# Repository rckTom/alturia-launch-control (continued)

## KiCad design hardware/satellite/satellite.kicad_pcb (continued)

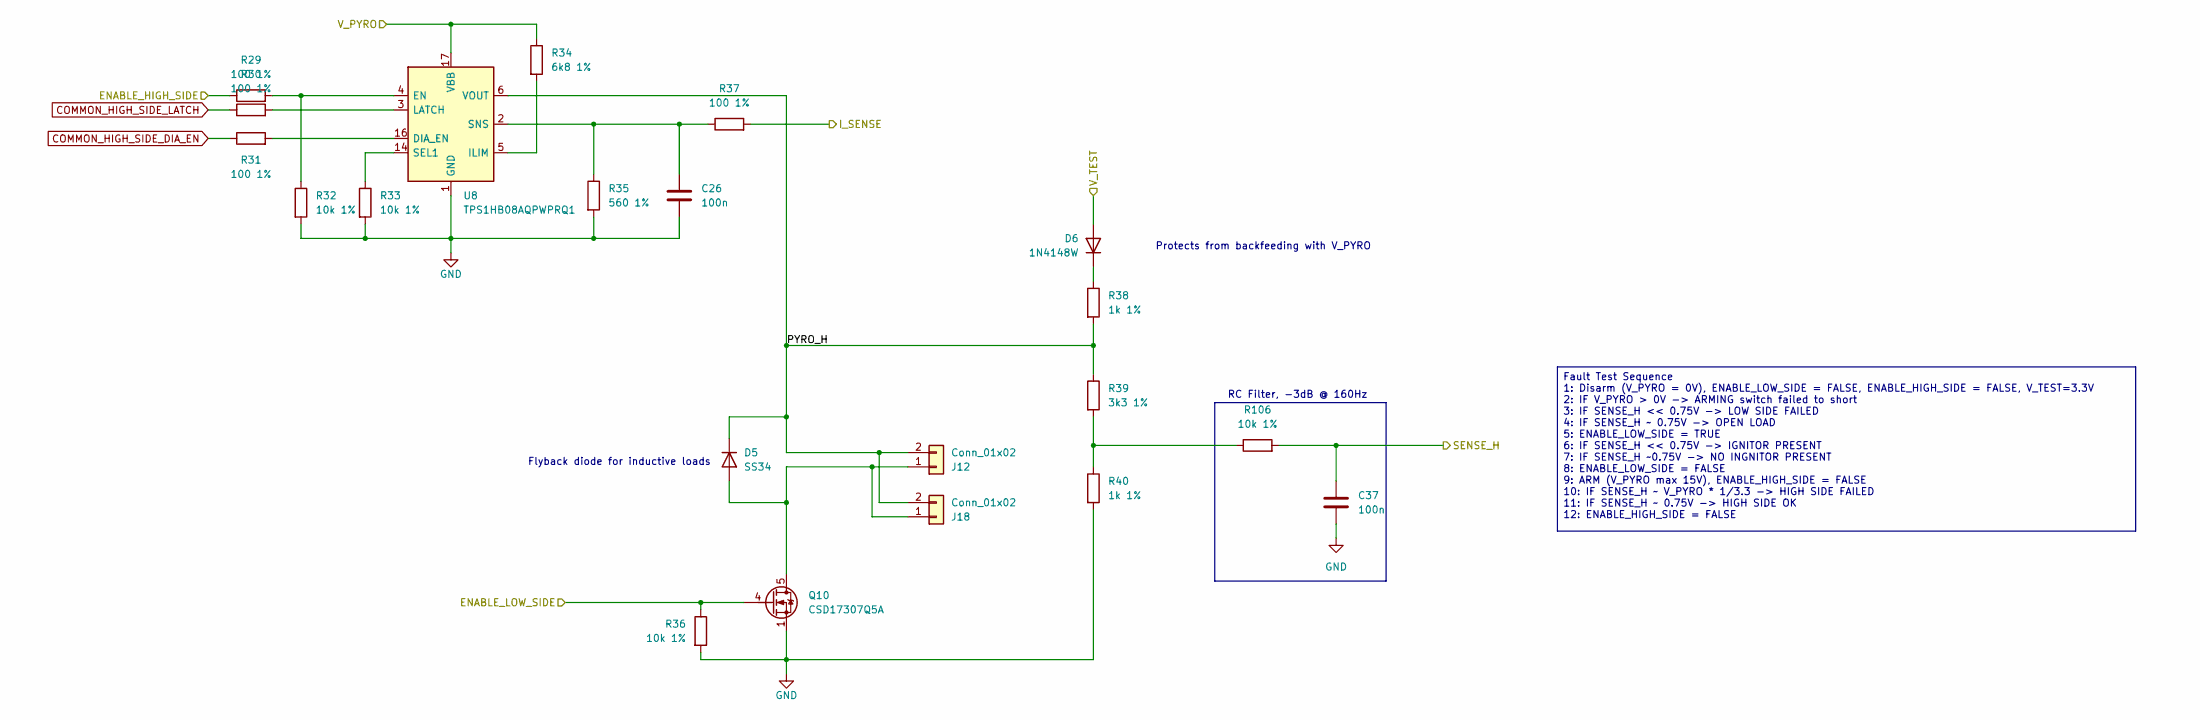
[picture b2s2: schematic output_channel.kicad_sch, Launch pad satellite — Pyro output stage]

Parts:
C26, C37: 100n; C_0603_1608Metric; LCSC C14663
D5: SS34; D_SMA; LCSC C8678
D6: 1N4148W; D_SOD-123; LCSC C81598
J12: Conn_01x02; TerminalBlock_CUI_TB007-508-02_1x02_P5.08mm_Horizontal
J18: Conn_01x02; BananJack
Q10: CSD17307Q5A; TDSON-8-1; LCSC C139362
R29, R30, R31, R37: 100 1%; R_0603_1608Metric; LCSC C22775
R32, R33, R36, R106: 10k 1%; R_0603_1608Metric; LCSC C25804
R34: 6k8 1%; R_0603_1608Metric; LCSC C23212
R35: 560 1%; R_0603_1608Metric; LCSC C23204
R38, R40: 1k 1%; R_0603_1608Metric; LCSC C21190
R39: 3k3 1%; R_0603_1608Metric; LCSC C22978
U8: TPS1HB08AQPWPRQ1; HTSSOP-16-1EP_4.4x5mm_P0.65mm_EP3.4x5mm_Mask2.78x3.37mm_The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; MPN TPS1HB08AQPWPRQ1; LCSC Part C3019223

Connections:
/PyroStage3/PYRO_H: D5.1 (K), J12.2, J18.2, R38.2, R39.1, U8.6 (VOUT), U8.7 (VOUT), U8.8 (VOUT), U8.9 (VOUT), U8.10 (VOUT), U8.11 (VOUT)
COMMON_HIGH_SIDE_DIA_EN: R31.1; also elsewhere on the board
COMMON_HIGH_SIDE_LATCH: R30.1; also elsewhere on the board
ENABLE_P3_HIGH: R29.1; also elsewhere on the board
ENABLE_P3_LOW: Q10.4 (G), R36.1; also elsewhere on the board
GND: C26.2, C37.2, Q10.1 (S), Q10.2 (S), Q10.3 (S), R32.2, R33.2, R35.2, R36.2, R40.2, U8.1 (GND); also elsewhere on the board
unnamed: D5.2 (A), J12.1, J18.1, Q10.5 (D)
unnamed: D6.1 (K), R38.1
unnamed: R39.2, R40.1, R106.1
unnamed: R31.2, U8.16 (DIA_EN)
unnamed: R29.2, R32.1, U8.4 (EN)
unnamed: R34.2, U8.5 (ILIM)
unnamed: R30.2, U8.3 (LATCH)
unnamed: R33.1, U8.14 (SEL1)
unnamed: C26.1, R35.1, R37.1, U8.2 (SNS)
SENSE_H_P3: C37.1, R106.2; also elsewhere on the board
SENSE_I_P3: R37.2; also elsewhere on the board
V_PYRO_ARMED: R34.1, U8.17 (VBB); also elsewhere on the board
V_TEST: D6.2 (A); also elsewhere on the board

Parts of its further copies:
C27, C28, C29, C35, C36, C38, C39, C40, C41, C42: 100n; C_0603_1608Metric; LCSC C14663
D7, D9, D11, D13, D15: SS34; D_SMA; LCSC C8678
D8, D10, D12, D14, D16: 1N4148W; D_SOD-123; LCSC C81598
J13, J14, J15, J16, J17: Conn_01x02; TerminalBlock_CUI_TB007-508-02_1x02_P5.08mm_Horizontal
J19, J20, J21, J22, J23: Conn_01x02; BananJack
Q11, Q12, Q13, Q14, Q15: CSD17307Q5A; TDSON-8-1; LCSC C139362
R41, R42, R43, R49, R53, R54, R55, R61, R65, R66, R67, R73, R77, R78, R79, R85, R89, R90, R91, R97: 100 1%; R_0603_1608Metric; LCSC C22775
R44, R45, R48, R56, R57, R60, R68, R69, R72, R80, R81, R84, R92, R93, R96, R107, R108, R109, R110, R111: 10k 1%; R_0603_1608Metric; LCSC C25804
R46, R58, R70, R82, R94: 6k8 1%; R_0603_1608Metric; LCSC C23212
R47, R59, R71, R83, R95: 560 1%; R_0603_1608Metric; LCSC C23204
R50, R52, R62, R64, R74, R76, R86, R88, R98, R100: 1k 1%; R_0603_1608Metric; LCSC C21190
R51, R63, R75, R87, R99: 3k3 1%; R_0603_1608Metric; LCSC C22978
U9, U10, U11, U14, U15: TPS1HB08AQPWPRQ1; HTSSOP-16-1EP_4.4x5mm_P0.65mm_EP3.4x5mm_Mask2.78x3.37mm_The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; MPN TPS1HB08AQPWPRQ1; LCSC Part C3019223

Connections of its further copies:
/PyroStage1/PYRO_H: D15.1 (K), J17.2, J23.2, R98.2, R99.1, U15.6 (VOUT), U15.7 (VOUT), U15.8 (VOUT), U15.9 (VOUT), U15.10 (VOUT), U15.11 (VOUT)
/PyroStage2/PYRO_H: D13.1 (K), J16.2, J22.2, R86.2, R87.1, U14.6 (VOUT), U14.7 (VOUT), U14.8 (VOUT), U14.9 (VOUT), U14.10 (VOUT), U14.11 (VOUT)
/PyroStage4/PYRO_H: D7.1 (K), J13.2, J19.2, R50.2, R51.1, U9.6 (VOUT), U9.7 (VOUT), U9.8 (VOUT), U9.9 (VOUT), U9.10 (VOUT), U9.11 (VOUT)
/PyroStage5/PYRO_H: D9.1 (K), J14.2, J20.2, R62.2, R63.1, U10.6 (VOUT), U10.7 (VOUT), U10.8 (VOUT), U10.9 (VOUT), U10.10 (VOUT), U10.11 (VOUT)
/PyroStage6/PYRO_H: D11.1 (K), J15.2, J21.2, R74.2, R75.1, U11.6 (VOUT), U11.7 (VOUT), U11.8 (VOUT), U11.9 (VOUT), U11.10 (VOUT), U11.11 (VOUT)
COMMON_HIGH_SIDE_DIA_EN: R43.1, R55.1, R67.1, R79.1, R91.1; also elsewhere on the board
COMMON_HIGH_SIDE_LATCH: R42.1, R54.1, R66.1, R78.1, R90.1; also elsewhere on the board
ENABLE_P1_HIGH: R89.1; also elsewhere on the board
ENABLE_P1_LOW: Q15.4 (G), R96.1; also elsewhere on the board
ENABLE_P2_HIGH: R77.1; also elsewhere on the board
ENABLE_P2_LOW: Q14.4 (G), R84.1; also elsewhere on the board
ENABLE_P4_HIGH: R41.1; also elsewhere on the board
ENABLE_P4_LOW: Q11.4 (G), R48.1; also elsewhere on the board
ENABLE_P5_HIGH: R53.1; also elsewhere on the board
ENABLE_P5_LOW: Q12.4 (G), R60.1; also elsewhere on the board
ENABLE_P6_HIGH: R65.1; also elsewhere on the board
ENABLE_P6_LOW: Q13.4 (G), R72.1; also elsewhere on the board
GND: C27.2, C28.2, C29.2, C35.2, C36.2, C38.2, C39.2, C40.2, C41.2, C42.2, Q11.1 (S), Q11.2 (S), Q11.3 (S), Q12.1 (S), Q12.2 (S), Q12.3 (S), Q13.1 (S), Q13.2 (S), Q13.3 (S), Q14.1 (S), Q14.2 (S), Q14.3 (S), Q15.1 (S), Q15.2 (S), Q15.3 (S), R44.2, R45.2, R47.2, R48.2, R52.2, R56.2, R57.2, R59.2, R60.2, R64.2, R68.2, R69.2, R71.2, R72.2, R76.2, R80.2, R81.2, R83.2, R84.2, R88.2, R92.2, R93.2, R95.2, R96.2, R100.2, U9.1 (GND), U10.1 (GND), U11.1 (GND), U14.1 (GND), U15.1 (GND); also elsewhere on the board
unnamed: D7.2 (A), J13.1, J19.1, Q11.5 (D)
unnamed: D8.1 (K), R50.1
unnamed: D9.2 (A), J14.1, J20.1, Q12.5 (D)
unnamed: D10.1 (K), R62.1
unnamed: D11.2 (A), J15.1, J21.1, Q13.5 (D)
unnamed: D12.1 (K), R74.1
unnamed: D13.2 (A), J16.1, J22.1, Q14.5 (D)
unnamed: D14.1 (K), R86.1
unnamed: D15.2 (A), J17.1, J23.1, Q15.5 (D)
unnamed: D16.1 (K), R98.1
unnamed: R99.2, R100.1, R111.1
unnamed: R51.2, R52.1, R107.1
unnamed: R63.2, R64.1, R108.1
unnamed: R75.2, R76.1, R109.1
unnamed: R87.2, R88.1, R110.1
unnamed: R43.2, U9.16 (DIA_EN)
unnamed: R41.2, R44.1, U9.4 (EN)
unnamed: R46.2, U9.5 (ILIM)
unnamed: R42.2, U9.3 (LATCH)
unnamed: R45.1, U9.14 (SEL1)
unnamed: C27.1, R47.1, R49.1, U9.2 (SNS)
unnamed: R55.2, U10.16 (DIA_EN)
unnamed: R53.2, R56.1, U10.4 (EN)
unnamed: R58.2, U10.5 (ILIM)
unnamed: R54.2, U10.3 (LATCH)
unnamed: R57.1, U10.14 (SEL1)
unnamed: C28.1, R59.1, R61.1, U10.2 (SNS)
unnamed: R67.2, U11.16 (DIA_EN)
unnamed: R65.2, R68.1, U11.4 (EN)
unnamed: R70.2, U11.5 (ILIM)
unnamed: R66.2, U11.3 (LATCH)
unnamed: R69.1, U11.14 (SEL1)
unnamed: C29.1, R71.1, R73.1, U11.2 (SNS)
unnamed: R79.2, U14.16 (DIA_EN)
unnamed: R77.2, R80.1, U14.4 (EN)
unnamed: R82.2, U14.5 (ILIM)
unnamed: R78.2, U14.3 (LATCH)
unnamed: R81.1, U14.14 (SEL1)
unnamed: C35.1, R83.1, R85.1, U14.2 (SNS)
unnamed: R91.2, U15.16 (DIA_EN)
unnamed: R89.2, R92.1, U15.4 (EN)
unnamed: R94.2, U15.5 (ILIM)
unnamed: R90.2, U15.3 (LATCH)
unnamed: R93.1, U15.14 (SEL1)
unnamed: C36.1, R95.1, R97.1, U15.2 (SNS)
SENSE_H_P1: C42.1, R111.2; also elsewhere on the board
SENSE_H_P2: C41.1, R110.2; also elsewhere on the board
SENSE_H_P4: C38.1, R107.2; also elsewhere on the board
SENSE_H_P5: C39.1, R108.2; also elsewhere on the board
SENSE_H_P6: C40.1, R109.2; also elsewhere on the board
SENSE_I_P1: R97.2; also elsewhere on the board
SENSE_I_P2: R85.2; also elsewhere on the board
SENSE_I_P4: R49.2; also elsewhere on the board
SENSE_I_P5: R61.2; also elsewhere on the board
SENSE_I_P6: R73.2; also elsewhere on the board
V_PYRO_ARMED: R46.1, R58.1, R70.1, R82.1, R94.1, U9.17 (VBB), U10.17 (VBB), U11.17 (VBB), U14.17 (VBB), U15.17 (VBB); also elsewhere on the board
V_TEST: D8.2 (A), D10.2 (A), D12.2 (A), D14.2 (A), D16.2 (A); also elsewhere on the board

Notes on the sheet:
Protects from backfeeding with V_PYRO
Flyback diode for inductive loads
RC Filter, -3dB @ 160Hz
Fault Test Sequence 1: Disarm (V_PYRO = 0V), ENABLE_LOW_SIDE = FALSE, ENABLE_HIGH_SIDE = FALSE, V_TEST=3.3V 2: IF V_PYRO > 0V -> ARMING switch failed to short 3: IF SENSE_H << 0.75V -> LOW SIDE FAILED 4: IF SENSE_H ~ 0.75V -> OPEN LOAD 5: ENABLE_LOW_SIDE = TRUE 6: IF SENSE_H << 0.75V -> IGNITOR PRE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

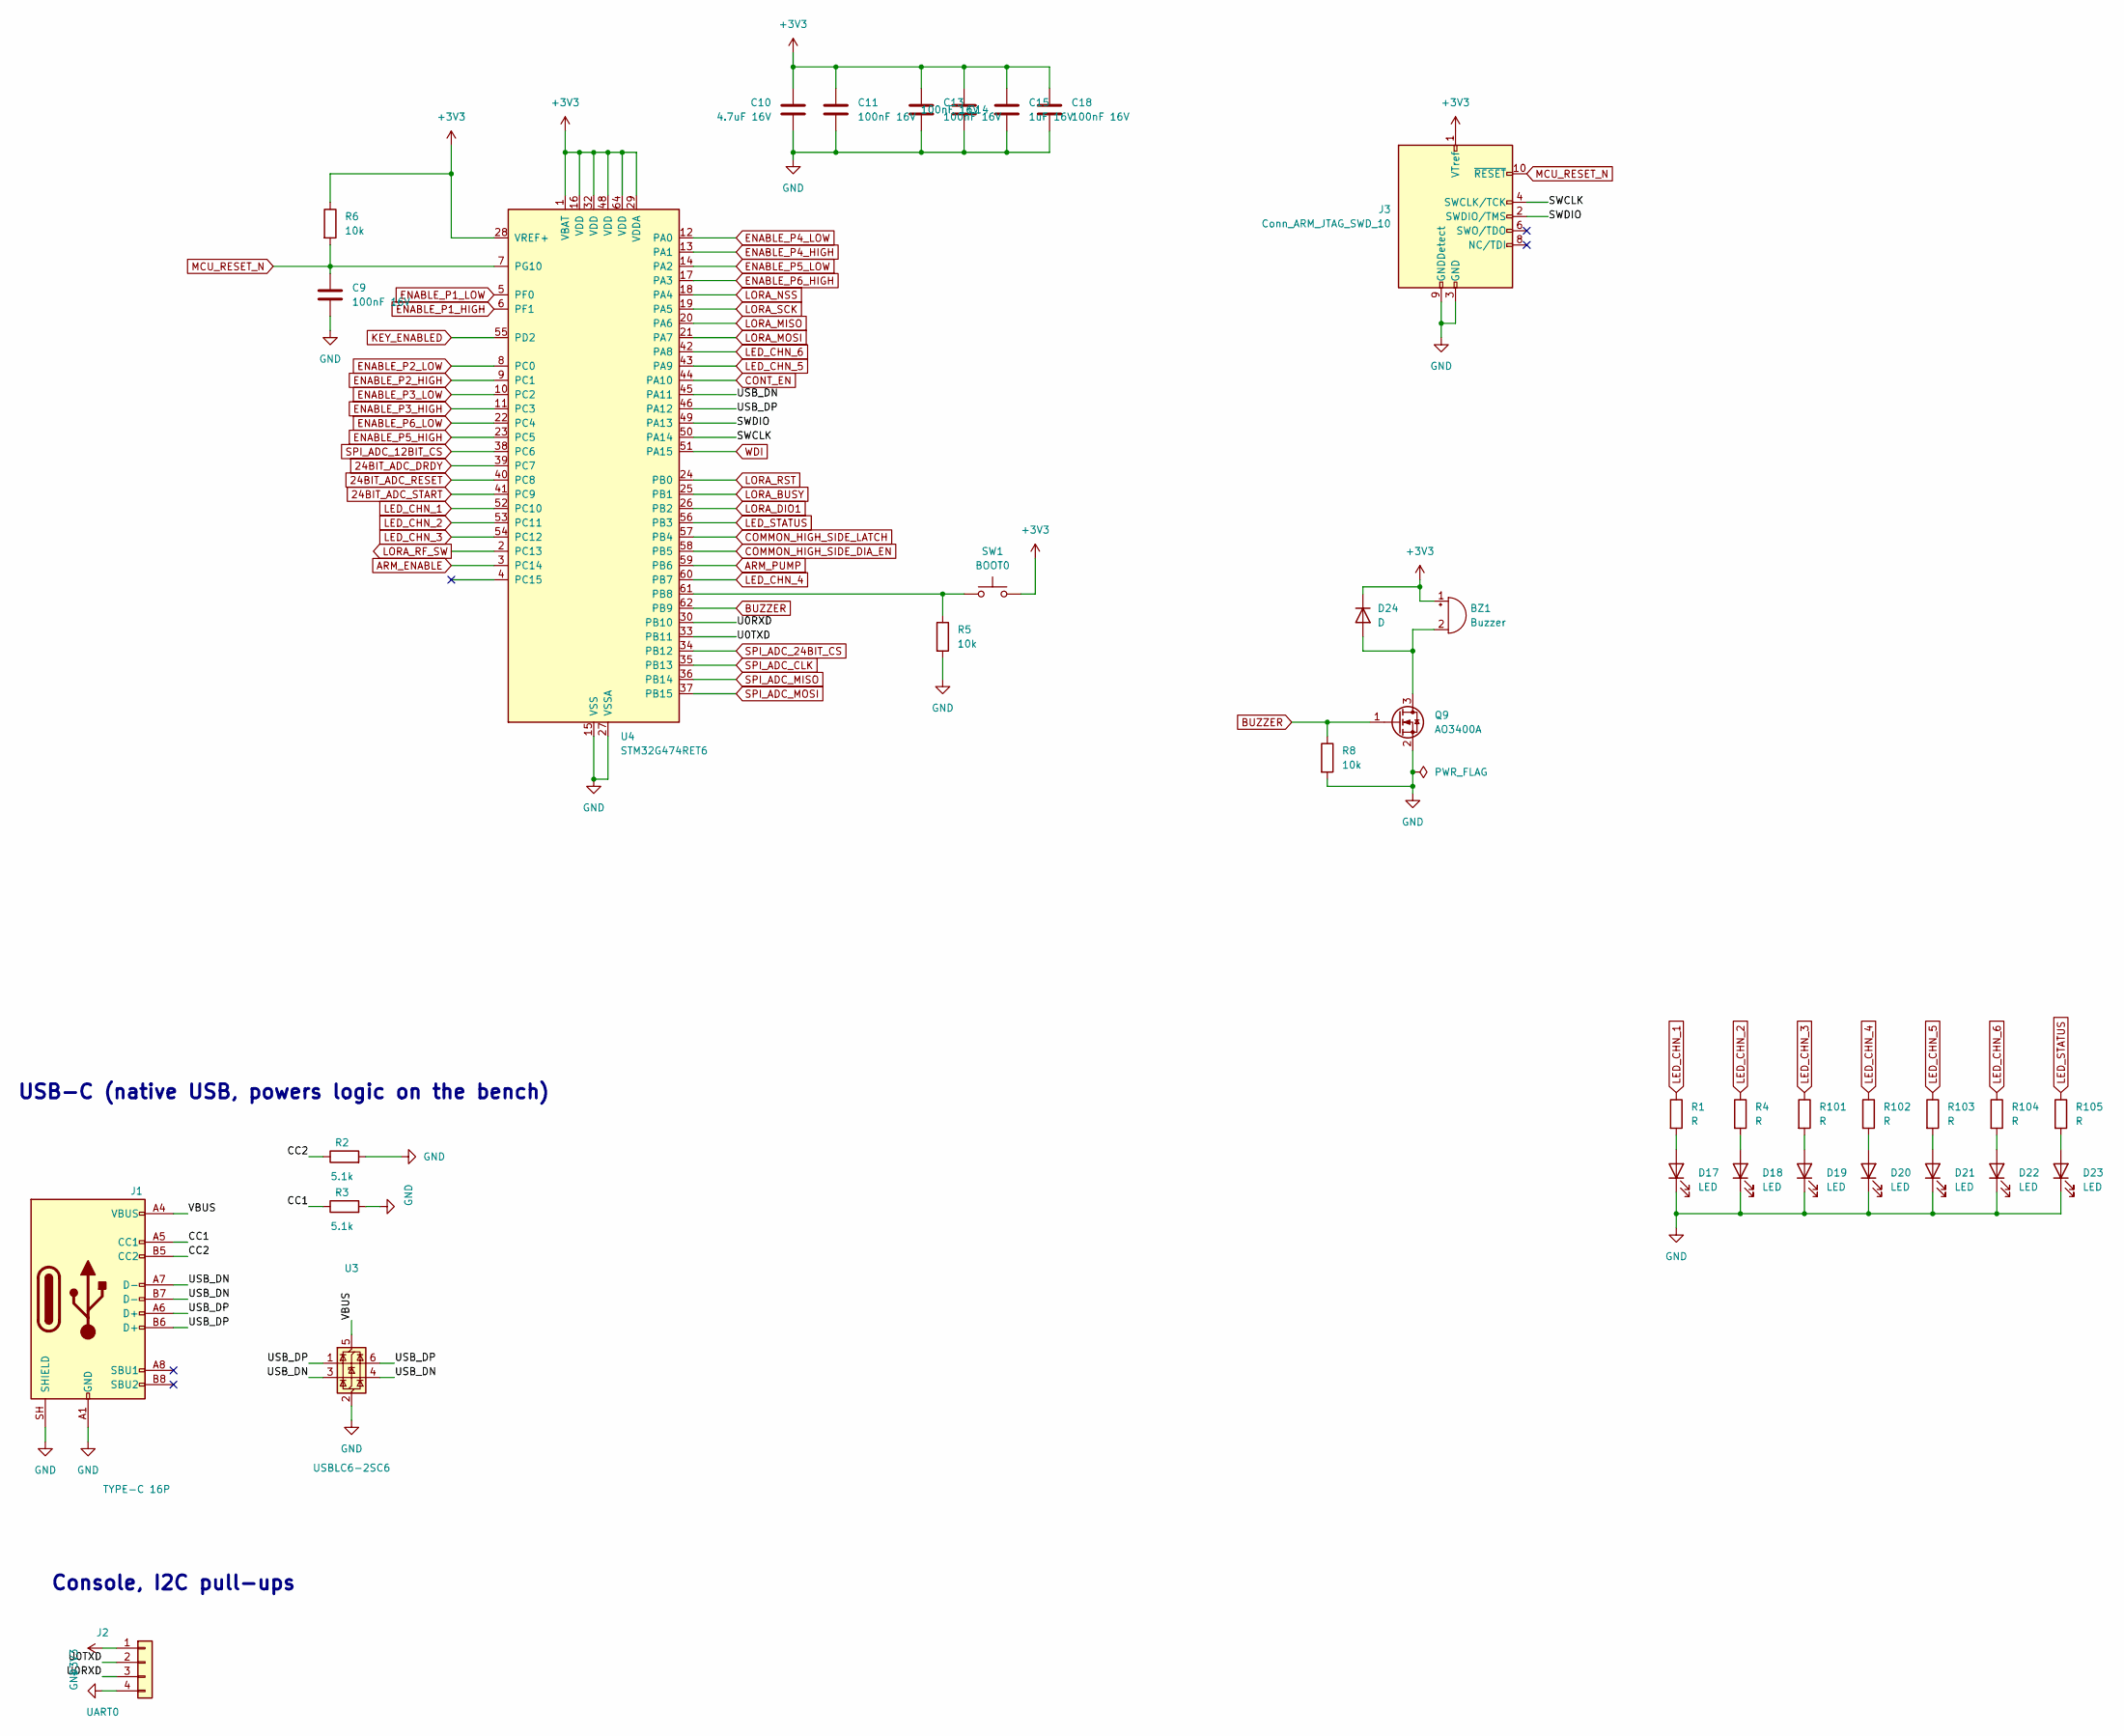
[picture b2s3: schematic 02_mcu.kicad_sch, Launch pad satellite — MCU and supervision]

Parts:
BZ1: Buzzer; Buzzer_12x9.5RM7.6
C9: 100nF 16V; C_0603_1608Metric
C10: 4.7uF 16V; C_0805_2012Metric
C11, C13, C14, C18: 100nF 16V; C_0402_1005Metric
C15: 1uF 16V; C_0603_1608Metric
D17, D18, D19, D20, D21, D22, D23: LED; LED_D5.0mm
D24: D; D_0805_2012Metric
J1: TYPE-C 16P; USB_C_Receptacle_HRO_TYPE-C-31-M-12; LCSC C2765186
J2: UART0; PinHeader_1x04_P2.54mm_Vertical
J3: Conn_ARM_JTAG_SWD_10; PinHeader_2x05_P2.54mm_Vertical_SMD
Q9: AO3400A; SOT-23; LCSC C20917
R1, R4, R101, R102, R103, R104, R105: R; R_0603_1608Metric
R2, R3: 5.1k; R_0603_1608Metric; LCSC C23186
R5: 10k; R_0402_1005Metric
R6, R8: 10k; R_0603_1608Metric
SW1: BOOT0; SW_SPST_TL3342
U3: USBLC6-2SC6; SOT-23-6; LCSC C2687116
U4: STM32G474RET6; LQFP-64_10x10mm_P0.5mm; MPN STM32G474RET6

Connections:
24BIT_ADC_DRDY: U4.39 (PC7); also elsewhere on the board
24BIT_ADC_RESET: U4.40 (PC8); also elsewhere on the board
24BIT_ADC_START: U4.41 (PC9); also elsewhere on the board
+3V3: BZ1.1 (+), C10.1, C11.1, C13.1, C14.1, C15.1, C18.1, D24.1 (K), J2.1, J3.1 (VTref), R6.1, SW1.2, U4.1 (VBAT), U4.16 (VDD), U4.28 (VREF+), U4.29 (VDDA), U4.32 (VDD), U4.48 (VDD), U4.64 (VDD); also elsewhere on the board
/mcu/CC1: J1.A5 (CC1), R3.1
/mcu/CC2: J1.B5 (CC2), R2.1
/mcu/SWCLK: J3.4 (SWCLK/TCK), U4.50 (PA14)
/mcu/SWDIO: J3.2 (SWDIO/TMS), U4.49 (PA13)
/mcu/U0RXD: J2.3, U4.30 (PB10)
/mcu/U0TXD: J2.2, U4.33 (PB11)
/mcu/USB_DN: J1.A7 (D-), J1.B7 (D-), U3.3 (I/O2), U3.4 (I/O2), U4.45 (PA11)
/mcu/USB_DP: J1.A6 (D+), J1.B6 (D+), U3.1 (I/O1), U3.6 (I/O1), U4.46 (PA12)
/mcu/VBUS: J1.A4 (VBUS), J1.A9 (VBUS), J1.B4 (VBUS), J1.B9 (VBUS), U3.5 (VBUS)
ARM_ENABLE: U4.3 (PC14); also elsewhere on the board
ARM_PUMP: U4.59 (PB6); also elsewhere on the board
BUZZER: Q9.1 (G), R8.1, U4.62 (PB9)
COMMON_HIGH_SIDE_DIA_EN: U4.58 (PB5); also elsewhere on the board
COMMON_HIGH_SIDE_LATCH: U4.57 (PB4); also elsewhere on the board
CONT_EN: U4.44 (PA10); also elsewhere on the board
CONT_TEST_REQ: U4.4 (PC15); also elsewhere on the board
ENABLE_P1_HIGH: U4.6 (PF1); also elsewhere on the board
ENABLE_P1_LOW: U4.5 (PF0); also elsewhere on the board
ENABLE_P2_HIGH: U4.9 (PC1); also elsewhere on the board
ENABLE_P2_LOW: U4.8 (PC0); also elsewhere on the board
ENABLE_P3_HIGH: U4.11 (PC3); also elsewhere on the board
ENABLE_P3_LOW: U4.10 (PC2); also elsewhere on the board
ENABLE_P4_HIGH: U4.13 (PA1); also elsewhere on the board
ENABLE_P4_LOW: U4.12 (PA0); also elsewhere on the board
ENABLE_P5_HIGH: U4.23 (PC5); also elsewhere on the board
ENABLE_P5_LOW: U4.14 (PA2); also elsewhere on the board
ENABLE_P6_HIGH: U4.17 (PA3); also elsewhere on the board
ENABLE_P6_LOW: U4.22 (PC4); also elsewhere on the board
GND: C9.2, C10.2, C11.2, C13.2, C14.2, C15.2, C18.2, D17.1 (K), D18.1 (K), D19.1 (K), D20.1 (K), D21.1 (K), D22.1 (K), D23.1 (K), J1.A1 (GND), J1.A12 (GND), J1.B1 (GND), J1.B12 (GND), J1.SH (SHIELD), J2.4, J3.3 (GND), J3.5 (GND), J3.9 (GNDDetect), Q9.2 (S), R2.2, R3.2, R5.2, R8.2, U3.2 (GND), U4.15 (VSS), U4.27 (VSSA), U4.31 (VSS), U4.47 (VSS), U4.63 (VSS); also elsewhere on the board
KEY_ENABLED: U4.55 (PD2); also elsewhere on the board
LED_CHN_1: R1.1, U4.52 (PC10)
LED_CHN_2: R4.1, U4.53 (PC11)
LED_CHN_3: R101.1, U4.54 (PC12)
LED_CHN_4: R102.1, U4.60 (PB7)
LED_CHN_5: R103.1, U4.43 (PA9)
LED_CHN_6: R104.1, U4.42 (PA8)
LED_STATUS: R105.1, U4.56 (PB3)
LORA_BUSY: U4.25 (PB1); also elsewhere on the board
LORA_DIO1: U4.26 (PB2); also elsewhere on the board
LORA_MISO: U4.20 (PA6); also elsewhere on the board
LORA_MOSI: U4.21 (PA7); also elsewhere on the board
LORA_NSS: U4.18 (PA4); also elsewhere on the board
LORA_RF_SW: U4.2 (PC13); also elsewhere on the board
LORA_RST: U4.24 (PB0); also elsewhere on the board
LORA_SCK: U4.19 (PA5); also elsewhere on the board
MCU_RESET_N: C9.1, J3.10 (~RESET), R6.2, U4.7 (PG10)
unnamed: BZ1.2 (-), D24.2 (A), Q9.3 (D)
unnamed: D17.2 (A), R1.2
unnamed: D18.2 (A), R4.2
unnamed: D19.2 (A), R101.2
unnamed: D20.2 (A), R102.2
unnamed: D21.2 (A), R103.2
unnamed: D22.2 (A), R104.2
unnamed: D23.2 (A), R105.2
unnamed: R5.1, SW1.1, U4.61 (PB8)
SPI_ADC_12BIT_CS: U4.38 (PC6); also elsewhere on the board
SPI_ADC_24BIT_CS: U4.34 (PB12); also elsewhere on the board
SPI_ADC_CLK: U4.35 (PB13); also elsewhere on the board
SPI_ADC_MISO: U4.36 (PB14); also elsewhere on the board
SPI_ADC_MOSI: U4.37 (PB15); also elsewhere on the board

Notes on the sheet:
Console, I2C pull-ups
USB-C (native USB, powers logic on the bench)

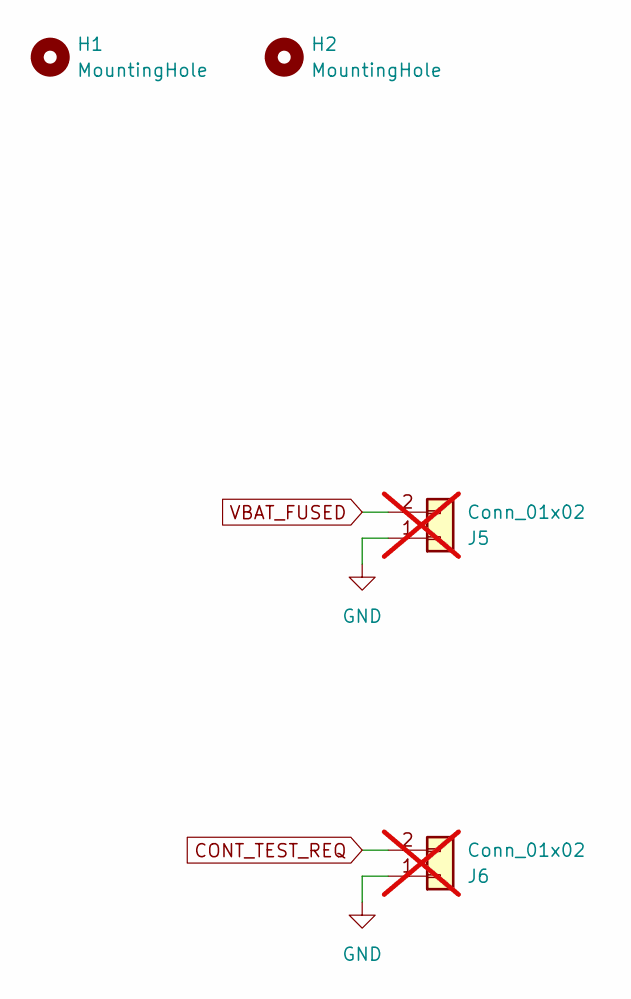
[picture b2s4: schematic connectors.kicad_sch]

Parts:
H1, H2: MountingHole; MountingHole_3.2mm_M3_ISO7380
J5: Conn_01x02; AMASS_XT60-M_1x02_P7.20mm_Vertical; LCSC C5334533; not fitted
J6: Conn_01x02; Molex_KK-254_AE-6410-02A_1x02_P2.54mm_Vertical; LCSC C5334533; not fitted

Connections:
CONT_TEST_REQ: J6.2; also elsewhere on the board
GND: J5.1, J6.1; also elsewhere on the board
VBAT_FUSED: J5.2; also elsewhere on the board

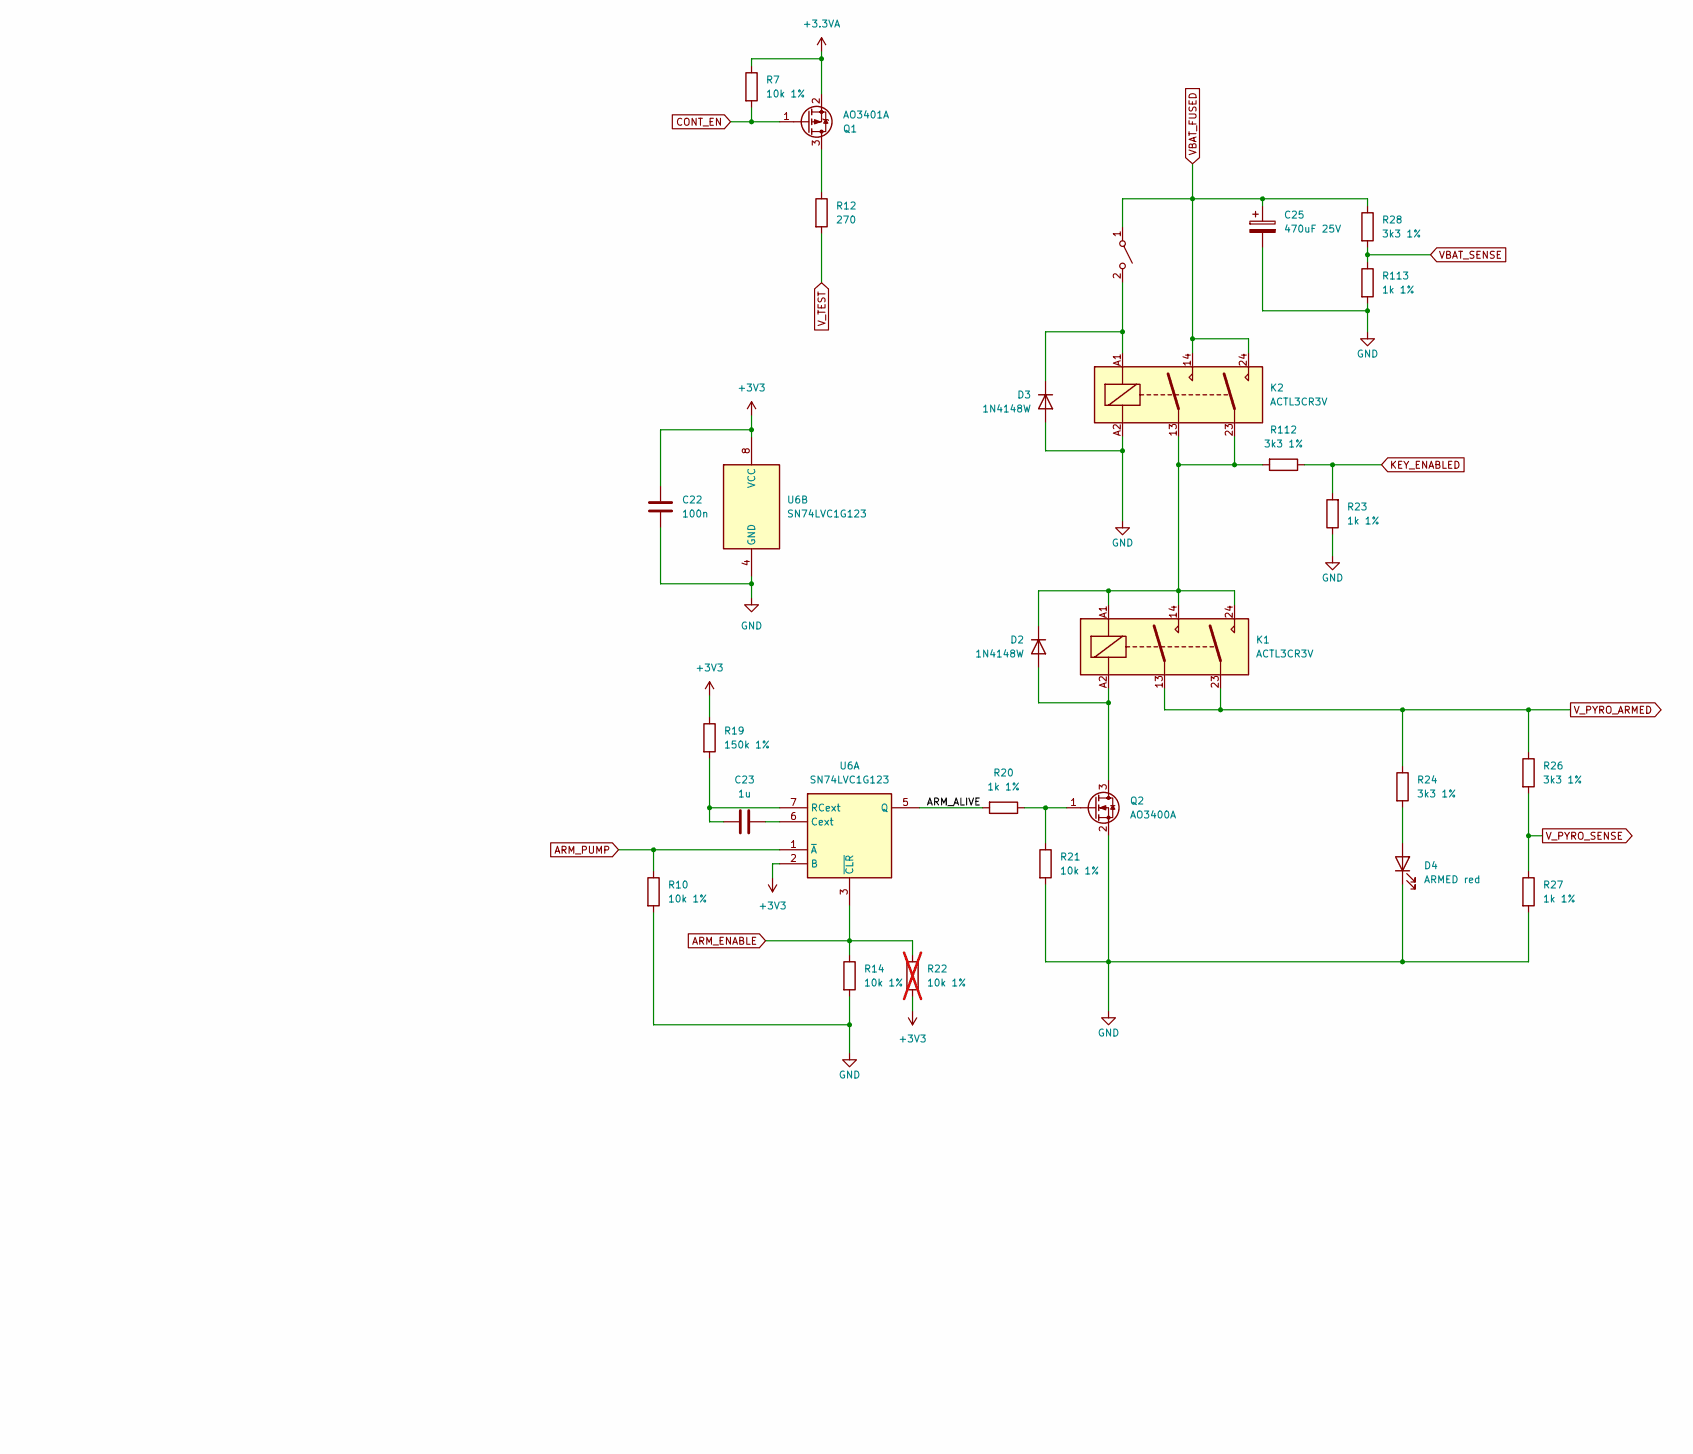
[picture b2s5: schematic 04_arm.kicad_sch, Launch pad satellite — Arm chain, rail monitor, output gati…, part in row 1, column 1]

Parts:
C22: 100n; C_0603_1608Metric; LCSC C14663
C23: 1u; C_0603_1608Metric; LCSC C5199872
C25: 470uF 25V; CP_Radial_D10.0mm_P7.50mm
D2, D3: 1N4148W; D_SOD-123; LCSC C81598
D4: ARMED red; LED_D5.0mm
K1, K2: ACTL3CR3V; RELAY-TH_ACTL3CR3; LCSC C6118826
Q1: AO3401A; SOT-23; LCSC C15127
Q2: AO3400A; SOT-23; LCSC C20917
R7, R10, R14, R21: 10k 1%; R_0603_1608Metric; LCSC C25804
R12: 270; R_0603_1608Metric; LCSC C22966
R19: 150k 1%; R_0603_1608Metric; LCSC C22807
R20, R23, R27, R113: 1k 1%; R_0603_1608Metric; LCSC C21190
R22: 10k 1%; R_0603_1608Metric; not fitted
R24, R26, R28, R112: 3k3 1%; R_0603_1608Metric; LCSC C22978
SW2: SW_SPST; Molex_KK-254_AE-6410-02A_1x02_P2.54mm_Vertical
U6: SN74LVC1G123; SSOP-8_2.95x2.8mm_P0.65mm; LCSC C123302

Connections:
+3.3VA: Q1.2 (S), R7.1; also elsewhere on the board
+3V3: C22.1, R19.1, R22.2, U6.2 (B), U6.8 (VCC); also elsewhere on the board
/arm/ARM_ALIVE: R20.2, U6.5 (Q)
ARM_ENABLE: R14.1, R22.1, U6.3 (~CLR); also elsewhere on the board
ARM_PUMP: R10.1, U6.1 (~A); also elsewhere on the board
CONT_EN: Q1.1 (G), R7.2; also elsewhere on the board
GND: C22.2, C25.2, D3.2 (A), D4.1 (K), K2.A2, Q2.2 (S), R10.2, R14.2, R21.2, R23.1, R27.2, R113.2, U6.4 (GND); also elsewhere on the board
KEY_ENABLED: R23.2, R112.1; also elsewhere on the board
unnamed: D2.2 (A), K1.A2, Q2.3 (D)
unnamed: D2.1 (K), K1.14, K1.24, K1.A1, K2.13, K2.23, R112.2
unnamed: D3.1 (K), K2.A1, SW2.2 (B)
unnamed: D4.2 (A), R24.2
unnamed: Q1.3 (D), R12.1
unnamed: Q2.1 (G), R20.1, R21.1
unnamed: C23.1, U6.6 (Cext)
unnamed: C23.2, R19.2, U6.7 (RCext)
VBAT_FUSED: C25.1, K2.14, K2.24, R28.1, SW2.1 (A); also elsewhere on the board
VBAT_SENSE: R28.2, R113.1; also elsewhere on the board
V_PYRO_ARMED: K1.13, K1.23, R24.1, R26.1; also elsewhere on the board
V_PYRO_SENSE: R26.2, R27.1; also elsewhere on the board
V_TEST: R12.2; also elsewhere on the board

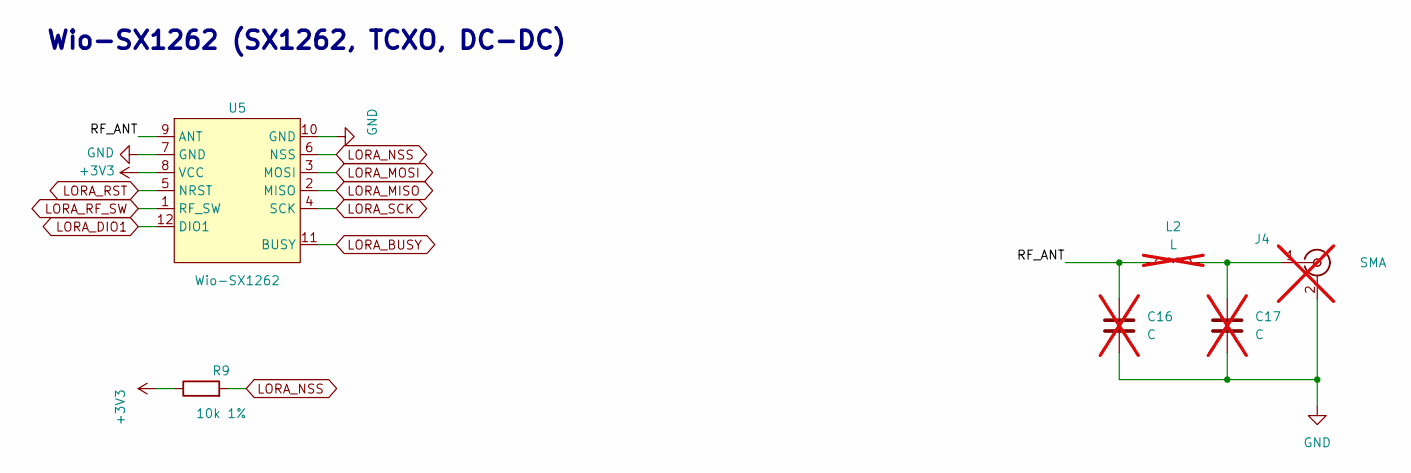
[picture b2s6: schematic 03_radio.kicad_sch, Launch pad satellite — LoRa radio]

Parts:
C16, C17: C; C_0603_1608Metric_Pad1.08x0.95mm_HandSolder; not fitted
J4: SMA; SMA_Amphenol_132291_Vertical; LCSC C496549; not fitted
L2: L; L_0603_1608Metric_Pad1.05x0.95mm_HandSolder; not fitted
R9: 10k 1%; R_0603_1608Metric; LCSC C25804
U5: Wio-SX1262; WIRELM-SMD_WIO-SX1262

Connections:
+3V3: R9.1, U5.8 (VCC); also elsewhere on the board
/radio/RF_ANT: C16.1, L2.1, U5.9 (ANT)
GND: C16.2, C17.2, J4.2 (Ext), U5.7 (GND), U5.10 (GND); also elsewhere on the board
LORA_BUSY: U5.11 (BUSY); also elsewhere on the board
LORA_DIO1: U5.12 (DIO1); also elsewhere on the board
LORA_MISO: U5.2 (MISO); also elsewhere on the board
LORA_MOSI: U5.3 (MOSI); also elsewhere on the board
LORA_NSS: R9.2, U5.6 (NSS); also elsewhere on the board
LORA_RF_SW: U5.1 (RF_SW); also elsewhere on the board
LORA_RST: U5.5 (NRST); also elsewhere on the board
LORA_SCK: U5.4 (SCK); also elsewhere on the board
unnamed: C17.1, J4.1 (In), L2.2

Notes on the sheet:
Wio-SX1262 (SX1262, TCXO, DC-DC)

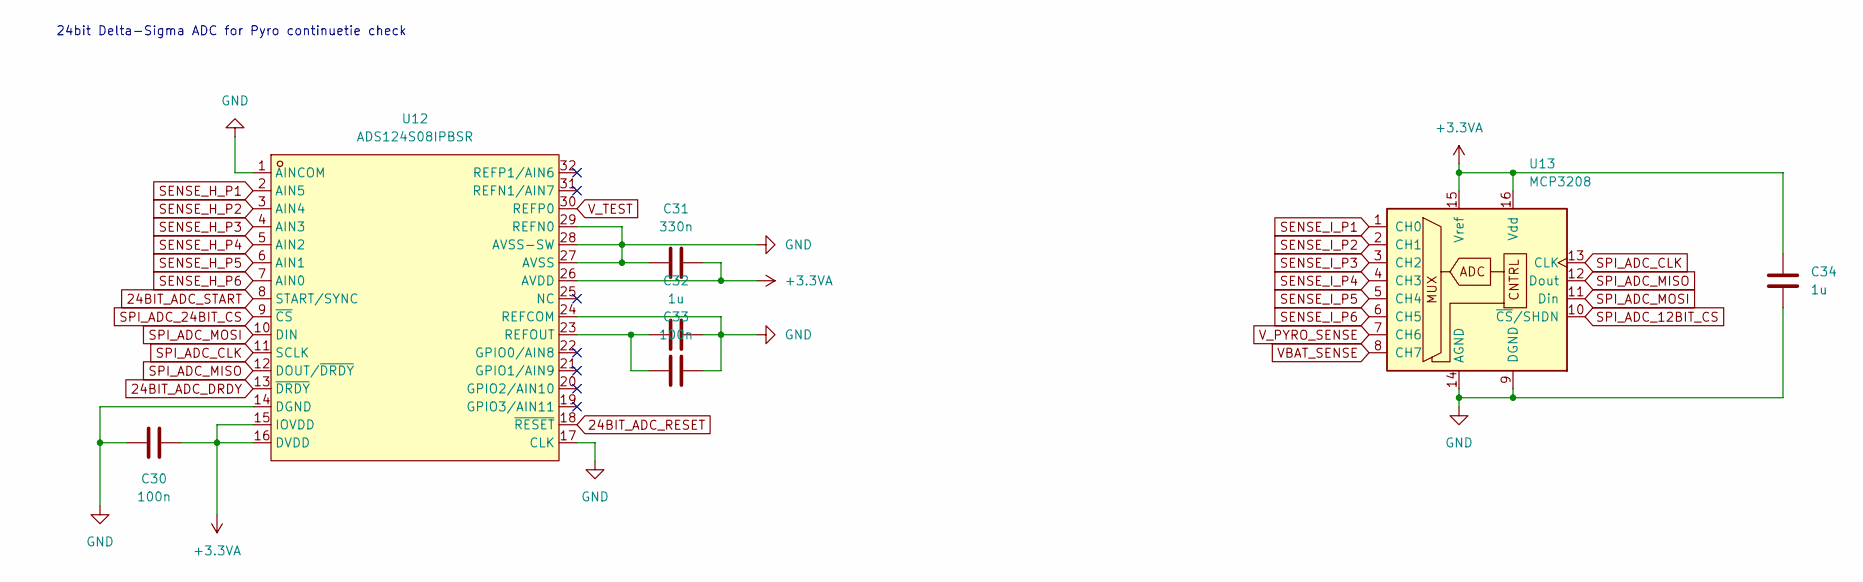
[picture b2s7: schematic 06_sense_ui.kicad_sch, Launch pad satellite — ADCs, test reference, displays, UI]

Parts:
C30, C33: 100n; C_0603_1608Metric; LCSC C14663
C31: 330n; C_0603_1608Metric; LCSC C107070
C32, C34: 1u; C_0603_1608Metric; LCSC C5199872
U12: ADS124S08IPBSR; TQFP-32_L5.0-W5.0-P0.50-LS7.0-TL; MPN ADS124S08IPBSR; LCSC Part C2870171
U13: MCP3208; SOIC-16_3.9x9.9mm_P1.27mm; LCSC C626764

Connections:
24BIT_ADC_DRDY: U12.13 (~DRDY); also elsewhere on the board
24BIT_ADC_RESET: U12.18 (~RESET); also elsewhere on the board
24BIT_ADC_START: U12.8 (START/SYNC); also elsewhere on the board
+3.3VA: C30.1, C31.1, C34.1, U12.15 (IOVDD), U12.16 (DVDD), U12.26 (AVDD), U13.15 (Vref), U13.16 (Vdd); also elsewhere on the board
GND: C30.2, C31.2, C32.1, C33.1, C34.2, U12.1 (AINCOM), U12.14 (DGND), U12.17 (CLK), U12.24 (REFCOM), U12.27 (AVSS), U12.28 (AVSS-SW), U12.29 (REFN0), U13.9 (DGND), U13.14 (AGND); also elsewhere on the board
unnamed: C32.2, C33.2, U12.23 (REFOUT)
SENSE_H_P1: U12.2 (AIN5); also elsewhere on the board
SENSE_H_P2: U12.3 (AIN4); also elsewhere on the board
SENSE_H_P3: U12.4 (AIN3); also elsewhere on the board
SENSE_H_P4: U12.5 (AIN2); also elsewhere on the board
SENSE_H_P5: U12.6 (AIN1); also elsewhere on the board
SENSE_H_P6: U12.7 (AIN0); also elsewhere on the board
SENSE_I_P1: U13.1 (CH0); also elsewhere on the board
SENSE_I_P2: U13.2 (CH1); also elsewhere on the board
SENSE_I_P3: U13.3 (CH2); also elsewhere on the board
SENSE_I_P4: U13.4 (CH3); also elsewhere on the board
SENSE_I_P5: U13.5 (CH4); also elsewhere on the board
SENSE_I_P6: U13.6 (CH5); also elsewhere on the board
SPI_ADC_12BIT_CS: U13.10 (~CS/SHDN); also elsewhere on the board
SPI_ADC_24BIT_CS: U12.9 (~CS); also elsewhere on the board
SPI_ADC_CLK: U12.11 (SCLK), U13.13 (CLK); also elsewhere on the board
SPI_ADC_MISO: U12.12 (DOUT/~DRDY), U13.12 (Dout); also elsewhere on the board
SPI_ADC_MOSI: U12.10 (DIN), U13.11 (Din); also elsewhere on the board
VBAT_SENSE: U13.8 (CH7); also elsewhere on the board
V_PYRO_SENSE: U13.7 (CH6); also elsewhere on the board
V_TEST: U12.30 (REFP0); also elsewhere on the board

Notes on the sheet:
24bit Delta-Sigma ADC for Pyro continuetie check
